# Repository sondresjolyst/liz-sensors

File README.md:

# ReadTempAndHumidity

## Garge Voltmeter

### Voltage Divider Calculation for Wemos D1 Mini

To measure a higher voltage than 3.3V using the Wemos D1 Mini's ADC port, you can create a voltage divider with 47kΩ and 4.7kΩ resistors.

#### Voltage Divider Formula

$`V_{out} = V_{in} \times \frac{R2}{(R1 + R2)}`$

##### Precision

The Wemos D1 Mini's ADC can read voltages between 0 and 3.3V and gives a 10-bit reading (0-1024).
To calculate the minimum precision in voltage, one need to divide the maximum voltage by the ADC resolution:
$`\text{Minimum precision} = \frac{3.3V}{1024} \approx 0.00322V`$

The voltage at the ADC pin is approximately 9.09% of the input voltage. When the ADC reading changes by one step (e.g., from 366 to 365), the input voltage changes by:

$`\Delta V_{in} \approx \Delta V_{ADC} \times \frac{R1 + R2}{R2}`$

$`\Delta V_{in} \approx 0.00322V \times \frac{47k\Omega + 4.7k\Omega}{4.7k\Omega} \approx 0.0355V`$

#### Given Values

- $`R1 = 47kΩ`$ (47000Ω)
- $`R2 = 4.7kΩ`$ (4700Ω)
- $`V_{out} = 3.3V`$ (ADC input maximum)

#### Calculate Maximum

$`V_{in} = \frac{V_{out} \times (R1 + R2)}{R2}`$

Plugging in the values:

$`V_{in} = \frac{3.3V \times (47000Ω + 4700Ω)}{4700Ω}`$

$`V_{in} = 3.3V \times \frac{51700Ω}{4700Ω}`$

$`V_{in} \approx 36.3V`$

### Power Consumption Calculation

To estimate the power consumption of the Wemos D1 Mini:

#### Current Draw

Assuming an average current draw of 80mA (0.08A) when performing computations and connected to Wi-Fi.

#### Power Calculation

Using a 5V supply voltage:
$`\text{Power (P)} = \text{Voltage (V)} \times \text{Current (I)}`$

$`P = 5V \times 0.08A = 0.4W`$

#### Battery Life Estimation

With a 13V battery converted to 5V, taking into account the efficiency of the DC-DC converter (assumed to be 90% efficient):

$`\text{Effective Power Required} = \frac{\text{Power Consumption}}{\text{Efficiency}}`$

$`\text{Effective Power Required} = \frac{0.4W}{0.9} \approx 0.444W`$

#### Battery Current

$`I_{13V} = \frac{0.444W}{13V} \approx 0.034A = 34mA`$

#### Battery Capacity

If using a 13V motorcycle battery with a 6Ah (6000mAh) capacity:

Estimated Runtime:

$`\text{Runtime} = \frac{\text{Battery Capacity}}{\text{Current Draw}}`$

$`\text{Runtime} = \frac{6000mAh}{34mA} \approx 176 \, \text{hours}`$

To keep the battery above 40% charge, use only 60% of the battery's capacity:

$`\text{Usable Capacity} = 0.6 \times 72Wh = 43.2Wh`$

Revised Runtime:

$`\text{Runtime} = \frac{43.2Wh}{0.4W} = 108 \, \text{hours}`$

## Garge Sensor BME280

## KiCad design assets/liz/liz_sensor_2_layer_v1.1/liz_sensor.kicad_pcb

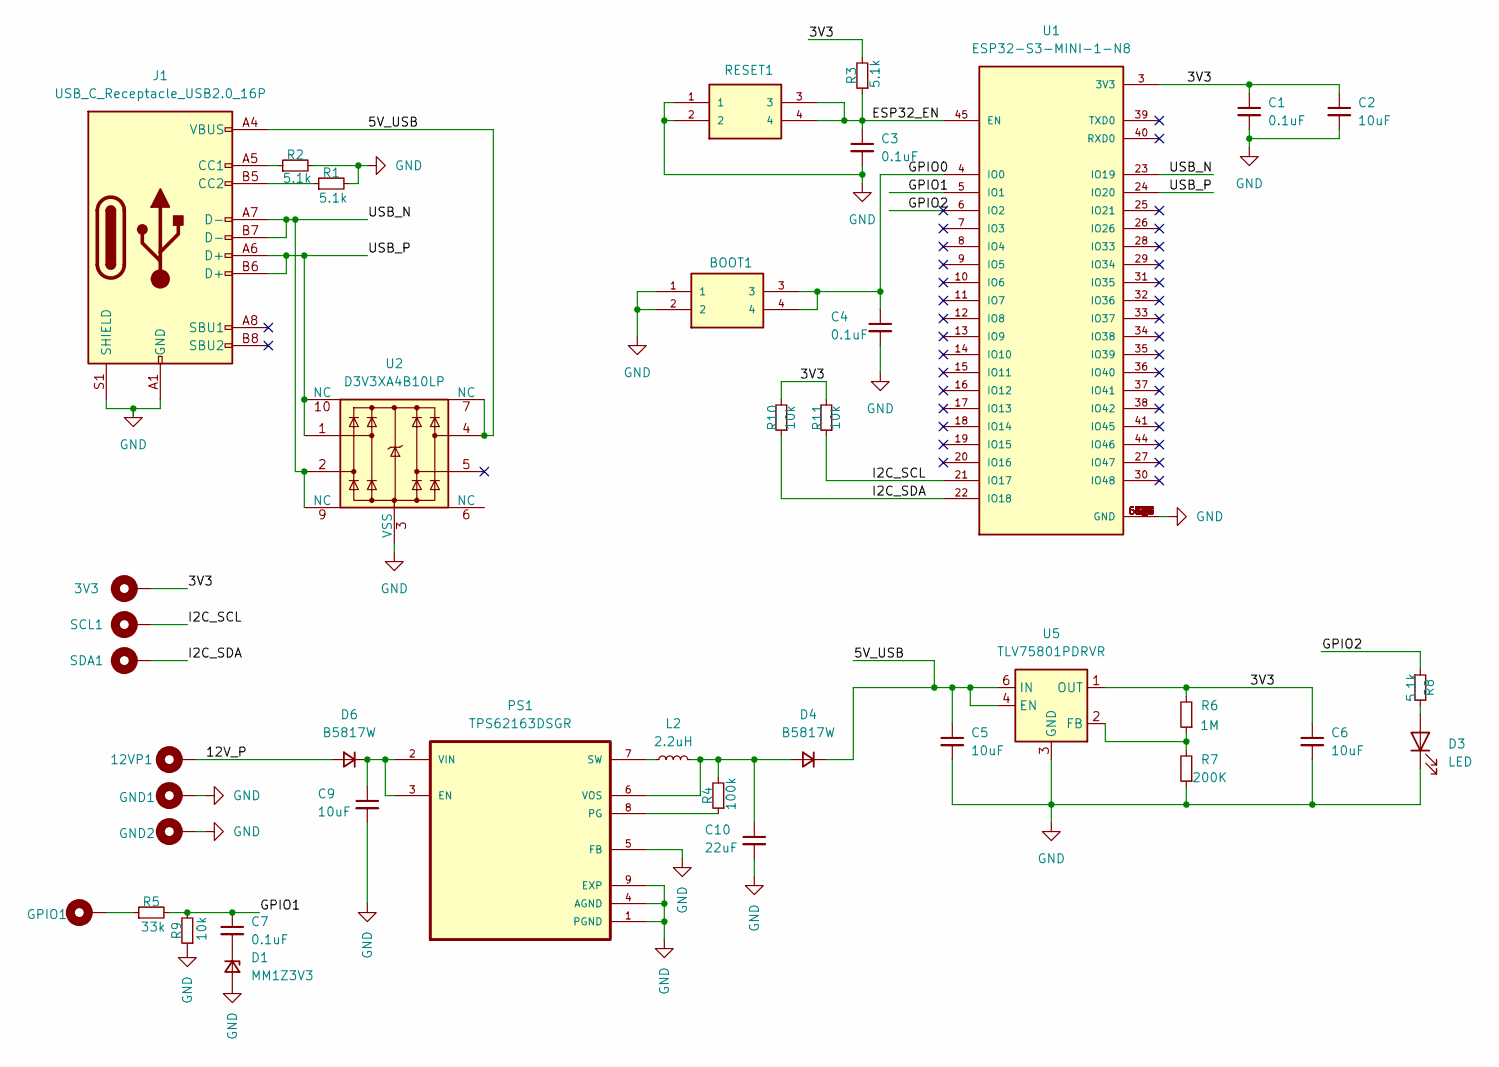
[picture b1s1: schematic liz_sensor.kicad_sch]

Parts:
3V3, 12VP1: TestPoint_THTPad_D1.0mm_Drill0.5mm
BOOT1: PTS810SJM250SMTRLFS; PTS810SJG250SMTRLFS; MANUFACTURER_PART_NUMBER PTS810SJK250SMTRLFS; JLCPCB Part # C116501
C1, C3, C4, C7: 0.1uF; C_0603_1608Metric; Part# CC0603KRX7R7BB104; JLCPCB Part # C108079
C2, C5, C6: 10uF; C_0603_1608Metric; Part# CL10A106KQ8NNNC; JLCPCB Part # C95839
C9: 10uF; C_0603_1608Metric; Part# CL10X106MO8NRNC; JLCPCB Part # C3039688
C10: 22uF; C_0603_1608Metric; Part# CL10A226MP8NUNE; JLCPCB Part # C86295
D1: MM1Z3V3; D_SOD-123; Part# MM1Z3V3; JLCPCB Part # C22379456
D3: LED; LED_0603_1608Metric; Part# HL-PST-1608H203BC; JLCPCB Part # C497940
D4, D6: B5817W; D_SOD-123; Part# B5817W; JLCPCB Part # C7420328
GND1, GND2: TestPoint_THTPad_D1.0mm_Drill0.5mm
GPIO1: TestPoint_THTPad_D1.0mm_Drill0.5mm
J1: USB_C_Receptacle_USB2.0_16P; USB_C_Receptacle_GCT_USB4105-xx-A_16P_TopMnt_Horizontal; Part# GT-USB-7010ASV; JLCPCB Part # C2988369
L2: 2.2uH; RES_CIGT201610_SAM; Part# WIP201610P-2R2ML; JLCPCB Part # C315717
PS1: TPS62163DSGR; DSG0008A; PARTREV E; JLCPCB Part # C97534
R1, R2, R3, R8: 5.1k; R_0603_1608Metric; Part# RC0603FR-075K1L; JLCPCB Part # C105580
R4: 100k; R_0603_1608Metric; Part# RC0603FR-07100KL; JLCPCB Part # C14675
R5: 33k; R_0603_1608Metric; Part# RC0603FR-0733KL; JLCPCB Part # C126359
R6: 1M; R_0603_1608Metric; Part# RC0603FR-071ML; JLCPCB Part # C105578
R7: 200K; R_0603_1608Metric; Part# RC0603FR-07200KL; JLCPCB Part # C105574
R9, R10, R11: 10k; R_0603_1608Metric; Part# RC0603FR-0710KL; JLCPCB Part # C98220
RESET1: PTS810SJM250SMTRLFS; PTS810SJG250SMTRLFS; MANUFACTURER_PART_NUMBER PTS810SJK250SMTRLFS; JLCPCB Part # C116501
SCL1: TestPoint_THTPad_D1.0mm_Drill0.5mm
SDA1: TestPoint_THTPad_D1.0mm_Drill0.5mm
U1: ESP32-S3-MINI-1-N8; XCVR_ESP32-S3-MINI-1-N8; PARTREV v0.6; JLCPCB Part # C2913206
U2: D3V3XA4B10LP; Diodes_UDFN-10_1.0x2.5mm_P0.5mm; Part# D3V3XA4B10LP-7; JLCPCB Part # C1980462
U5: TLV75801PDRVR; WSON-6-1EP_2x2mm_P0.65mm_EP1x1.6mm; Part# TLV75801PDRVR; JLCPCB Part # C2876308

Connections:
/3V3: 3V3.1, C1.1, C2.1, C6.1, R3.2, R6.2, R10.2, R11.2, U1.3 (3V3), U5.1 (OUT)
/5V_USB: C5.1, D4.1 (K), J1.A4 (VBUS), J1.A9 (VBUS), J1.B4 (VBUS), J1.B9 (VBUS), U2.4, U2.7 (NC), U5.4 (EN), U5.6 (IN)
/12V_P: 12VP1.1, D6.2 (A)
/ESP32_EN: C3.1, R3.1, RESET1.3, RESET1.4, U1.45 (EN)
/GPIO0: BOOT1.3, BOOT1.4, C4.1, U1.4 (IO0)
/GPIO1: C7.1, R5.2, R9.2, U1.5 (IO1)
/GPIO2: R8.1, U1.6 (IO2)
/I2C_SCL: R11.1, SCL1.1, U1.21 (IO17)
/I2C_SDA: R10.1, SDA1.1, U1.22 (IO18)
/USB_N: J1.A7 (D-), J1.B7 (D-), U1.23 (IO19), U2.2, U2.9 (NC)
/USB_P: J1.A6 (D+), J1.B6 (D+), U1.24 (IO20), U2.1, U2.10 (NC)
GND: BOOT1.1, BOOT1.2, C1.2, C2.2, C3.2, C4.2, C5.2, C6.2, C9.2, C10.2, D1.2 (A), D3.1 (K), GND1.1, GND2.1, J1.A1 (GND), J1.A12 (GND), J1.B1 (GND), J1.B12 (GND), J1.S1 (SHIELD), PS1.1 (PGND), PS1.4 (AGND), PS1.5 (FB), PS1.9 (EXP), R1.2, R2.2, R7.1, R9.1, RESET1.1, RESET1.2, U1.1 (GND), U1.2 (GND), U1.42 (GND), U1.43 (GND), U1.46 (GND), U1.47 (GND), U1.48 (GND), U1.49 (GND), U1.50 (GND), U1.51 (GND), U1.52 (GND), U1.53 (GND), U1.54 (GND), U1.55 (GND), U1.56 (GND), U1.57 (GND), U1.58 (GND), U1.59 (GND), U1.60 (GND), U1.61 (GND), U1.61_1 (GND), U1.61_2 (GND), U1.61_3 (GND), U1.61_4 (GND), U1.61_5 (GND), U1.61_6 (GND), U1.61_7 (GND), U1.61_8 (GND), U1.62 (GND), U1.63 (GND), U1.64 (GND), U1.65 (GND), U2.3 (VSS), U2.8 (VSS), U5.3 (GND), U5.7 (GND)
unnamed: C7.2, D1.1 (K)
unnamed: D3.2 (A), R8.2
unnamed: C10.1, D4.2 (A), L2.2, PS1.6 (VOS), R4.2
unnamed: C9.1, D6.1 (K), PS1.2 (VIN), PS1.3 (EN)
unnamed: GPIO1.1, R5.1
unnamed: J1.A5 (CC1), R2.1
unnamed: J1.B5 (CC2), R1.1
unnamed: PS1.8 (PG), R4.1
unnamed: L2.1, PS1.7 (SW)
unnamed: R6.1, R7.2, U5.2 (FB)

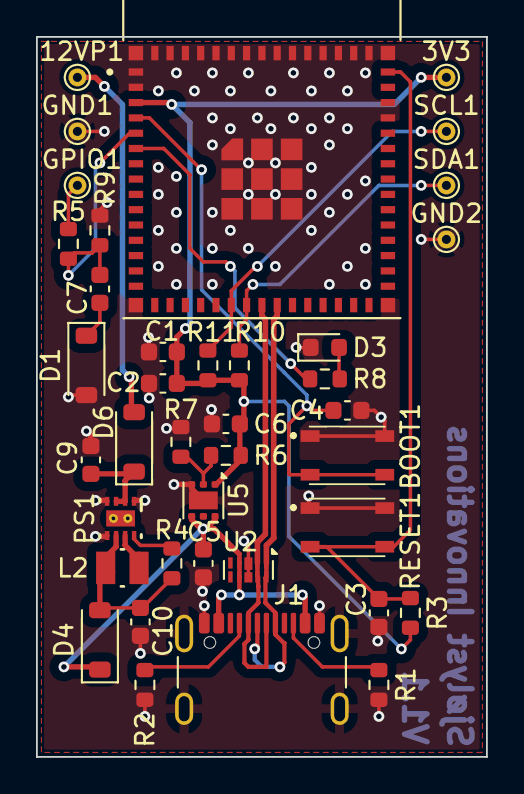
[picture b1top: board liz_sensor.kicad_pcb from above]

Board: 2 copper layers, 25.0 x 40.0 mm, 39 parts (0 on the bottom side), 22 nets.

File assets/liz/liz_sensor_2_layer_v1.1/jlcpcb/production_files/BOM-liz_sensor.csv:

Comment,Designator,Footprint,LCSC,Quantity
200K,R7,R_0603_1608Metric,C105574,1
1M,R6,R_0603_1608Metric,C105578,1
5.1k,"R1,R2,R3,R8",R_0603_1608Metric,C105580,4
0.1uF,"C1,C3,C4,C7",C_0603_1608Metric,C108079,4
PTS810SJM250SMTRLFS,"BOOT1,RESET1",PTS810SJG250SMTRLFS,C116501,2
33k,R5,R_0603_1608Metric,C126359,1
100k,R4,R_0603_1608Metric,C14675,1
D3V3XA4B10LP,U2,Diodes_UDFN-10_1.0x2.5mm_P0.5mm,C1980462,1
MM1Z3V3,D1,D_SOD-123,C22379456,1
TLV75801PDRVR,U5,WSON-6-1EP_2x2mm_P0.65mm_EP1x1.6mm,C2876308,1
ESP32-S3-MINI-1-N8,U1,XCVR_ESP32-S3-MINI-1-N8,C2913206,1
USB_C_Receptacle_USB2.0_16P,J1,USB_C_Receptacle_GCT_USB4105-xx-A_16P_TopMnt_Horizontal,C2988369,1
10uF,C9,C_0603_1608Metric,C3039688,1
2.2uH,L2,RES_CIGT201610_SAM,C315717,1
LED,D3,LED_0603_1608Metric,C497940,1
B5817W,"D4,D6",D_SOD-123,C7420328,2
22uF,C10,C_0603_1608Metric,C86295,1
10uF,"C2,C5,C6",C_0603_1608Metric,C95839,3
TPS62163DSGR,PS1,DSG0008A,C97534,1
10k,"R10,R11,R9",R_0603_1608Metric,C98220,3

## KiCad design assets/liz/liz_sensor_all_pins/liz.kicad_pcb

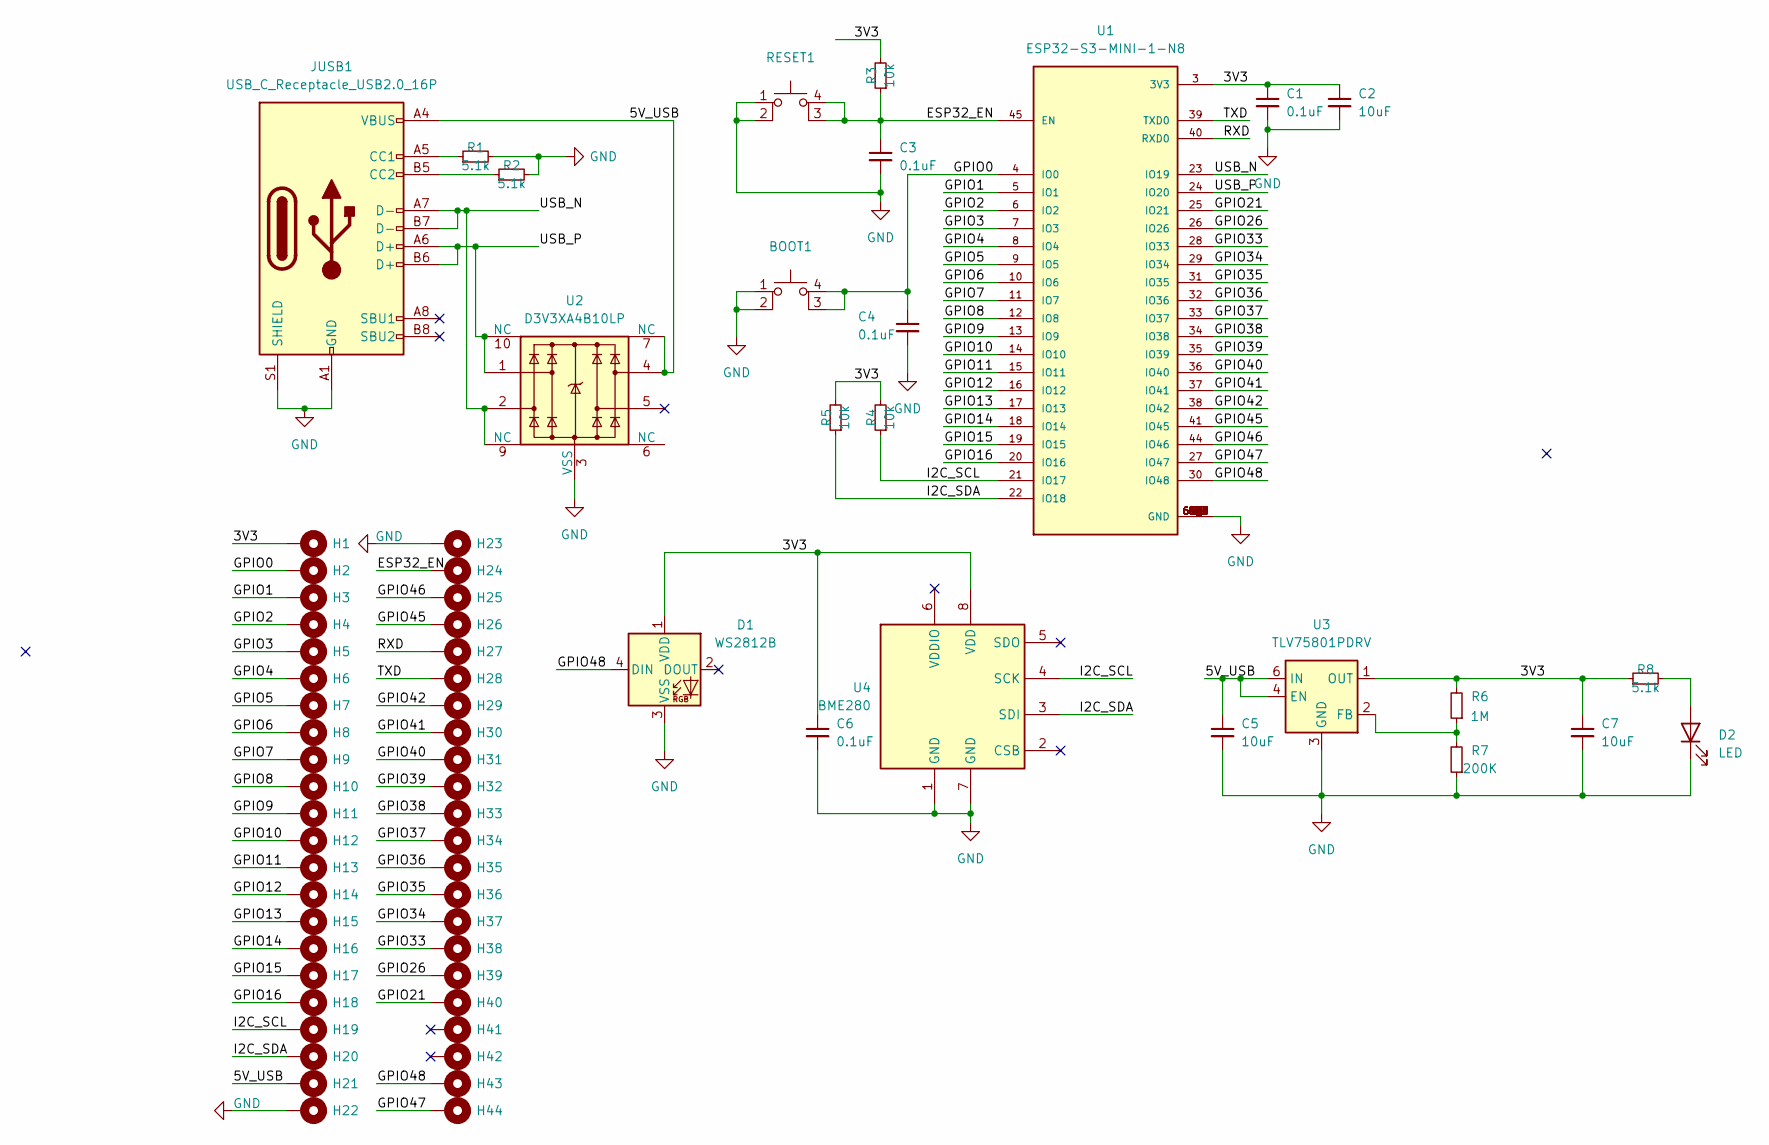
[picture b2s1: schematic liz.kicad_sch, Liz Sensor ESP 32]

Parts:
BOOT1: SW_SPST_PTS810
C1, C3, C4, C6: 0.1uF; C_0603_1608Metric
C2, C5, C7: 10uF; C_0603_1608Metric
D1: WS2812B; LED_WS2812B_PLCC4_5.0x5.0mm_P3.2mm
D2: LED; LED_0603_1608Metric
H1, H2, H3, H4, H5, H6, H7, H8, H9, H10, H11, H12, H13, H14, H15, H16, H17, H18, H19, H20, H21, H22, H23, H24, H25, H26, H27, H28, H29, H30, H31, H32, H33, H34, H35, H36, H37, H38, H39, H40, H41, H42, H43, H44: TestPoint_THTPad_D1.0mm_Drill0.5mm
JUSB1: USB_C_Receptacle_USB2.0_16P; USB_C_Receptacle_GCT_USB4105-xx-A_16P_TopMnt_Horizontal
R1, R2, R8: 5.1k; R_0603_1608Metric
R3, R4, R5: 10k; R_0603_1608Metric
R6: 1M; R_0603_1608Metric
R7: 200K; R_0603_1608Metric
RESET1: SW_SPST_PTS810
U1: ESP32-S3-MINI-1-N8; XCVR_ESP32-S3-MINI-1-N8; PARTREV v0.6
U2: D3V3XA4B10LP; Diodes_UDFN-10_1.0x2.5mm_P0.5mm
U3: TLV75801PDRV; WSON-6-1EP_2x2mm_P0.65mm_EP1x1.6mm
U4: BME280; Bosch_LGA-8_2.5x2.5mm_P0.65mm_ClockwisePinNumbering

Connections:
/3V3: C1.1, C2.1, C6.1, C7.1, D1.1 (VDD), H1.1, R3.2, R4.2, R5.2, R6.2, R8.1, U1.3 (3V3), U3.1 (OUT), U4.8 (VDD)
/5V_USB: C5.1, H21.1, JUSB1.A4 (VBUS), JUSB1.A9 (VBUS), JUSB1.B4 (VBUS), JUSB1.B9 (VBUS), U2.4, U2.7 (NC), U3.4 (EN), U3.6 (IN)
/ESP32_EN: C3.1, H24.1, R3.1, RESET1.3 (K), RESET1.4 (A), U1.45 (EN)
/GPIO0: BOOT1.3 (K), BOOT1.4 (A), C4.1, H2.1, U1.4 (IO0)
/GPIO1: H3.1, U1.5 (IO1)
/GPIO2: H4.1, U1.6 (IO2)
/GPIO3: H5.1, U1.7 (IO3)
/GPIO4: H6.1, U1.8 (IO4)
/GPIO5: H7.1, U1.9 (IO5)
/GPIO6: H8.1, U1.10 (IO6)
/GPIO7: H9.1, U1.11 (IO7)
/GPIO8: H10.1, U1.12 (IO8)
/GPIO9: H11.1, U1.13 (IO9)
/GPIO10: H12.1, U1.14 (IO10)
/GPIO11: H13.1, U1.15 (IO11)
/GPIO12: H14.1, U1.16 (IO12)
/GPIO13: H15.1, U1.17 (IO13)
/GPIO14: H16.1, U1.18 (IO14)
/GPIO15: H17.1, U1.19 (IO15)
/GPIO16: H18.1, U1.20 (IO16)
/GPIO21: H40.1, U1.25 (IO21)
/GPIO26: H39.1, U1.26 (IO26)
/GPIO33: H38.1, U1.28 (IO33)
/GPIO34: H37.1, U1.29 (IO34)
/GPIO35: H36.1, U1.31 (IO35)
/GPIO36: H35.1, U1.32 (IO36)
/GPIO37: H34.1, U1.33 (IO37)
/GPIO38: H33.1, U1.34 (IO38)
/GPIO39: H32.1, U1.35 (IO39)
/GPIO40: H31.1, U1.36 (IO40)
/GPIO41: H30.1, U1.37 (IO41)
/GPIO42: H29.1, U1.38 (IO42)
/GPIO45: H26.1, U1.41 (IO45)
/GPIO46: H25.1, U1.44 (IO46)
/GPIO47: H44.1, U1.27 (IO47)
/GPIO48: D1.4 (DIN), H43.1, U1.30 (IO48)
/I2C_SCL: H19.1, R4.1, U1.21 (IO17), U4.4 (SCK)
/I2C_SDA: H20.1, R5.1, U1.22 (IO18), U4.3 (SDI)
/RXD: H27.1, U1.40 (RXD0)
/TXD: H28.1, U1.39 (TXD0)
/USB_N: JUSB1.A7 (D-), JUSB1.B7 (D-), U1.23 (IO19), U2.2, U2.9 (NC)
/USB_P: JUSB1.A6 (D+), JUSB1.B6 (D+), U1.24 (IO20), U2.1, U2.10 (NC)
GND: BOOT1.1, BOOT1.2, C1.2, C2.2, C3.2, C4.2, C5.2, C6.2, C7.2, D1.3 (VSS), D2.1 (K), H22.1, H23.1, JUSB1.A1 (GND), JUSB1.A12 (GND), JUSB1.B1 (GND), JUSB1.B12 (GND), JUSB1.S1 (SHIELD), R1.2, R2.2, R7.1, RESET1.1, RESET1.2, U1.1 (GND), U1.2 (GND), U1.42 (GND), U1.43 (GND), U1.46 (GND), U1.47 (GND), U1.48 (GND), U1.49 (GND), U1.50 (GND), U1.51 (GND), U1.52 (GND), U1.53 (GND), U1.54 (GND), U1.55 (GND), U1.56 (GND), U1.57 (GND), U1.58 (GND), U1.59 (GND), U1.60 (GND), U1.61 (GND), U1.61_1 (GND), U1.61_2 (GND), U1.61_3 (GND), U1.61_4 (GND), U1.61_5 (GND), U1.61_6 (GND), U1.61_7 (GND), U1.61_8 (GND), U1.62 (GND), U1.63 (GND), U1.64 (GND), U1.65 (GND), U2.3 (VSS), U2.8 (VSS), U3.3 (GND), U3.7 (GND), U4.1 (GND), U4.7 (GND)
unnamed: D2.2 (A), R8.2
unnamed: JUSB1.A5 (CC1), R1.1
unnamed: JUSB1.B5 (CC2), R2.1
unnamed: R6.1, R7.2, U3.2 (FB)

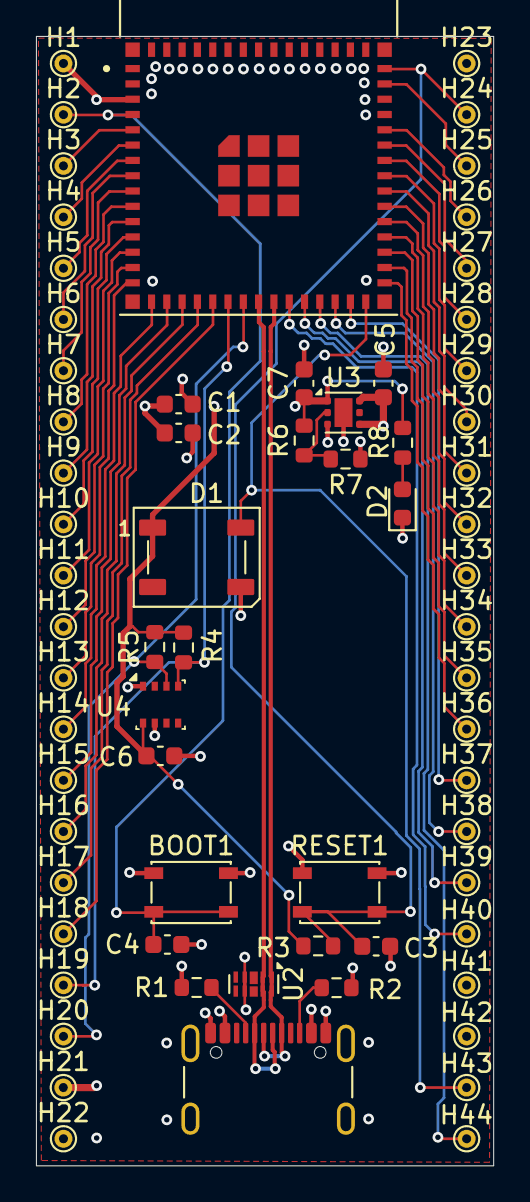
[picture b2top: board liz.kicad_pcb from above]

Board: 4 copper layers, 25.4 x 62.7 mm, 68 parts (0 on the bottom side), 47 nets.

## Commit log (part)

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2023-11-20 git setup
2023-11-26 controll device
2023-11-27 openwiz documentation
2023-12-03 format
2023-12-24 tempOffet, humidOffset, mqtt reconnect
2024-03-27 feat: add support for BME280 sensor
2024-04-20 feat: restart ESP if temp or humid fail 10 times
2024-11-24 feat: add voltmeter function
2024-11-24 chore(master): release 1.0.0
2024-12-01 chore: mqttcallback test
2024-12-03 ci: give lint contents read (#3)
    * ci: add linter and update release workflow
    * ci: give lint contents read
2024-12-03 ci: use commit hash instead of tag (#5)
2024-12-03 docs: circuit diagrams (#6)
    * docs: circuit diagrams
    * chore: add new line
2024-12-15 chore(deps): bump equinor/ops-actions from 9.11.0 to 9.12.1 (#8)
    Bumps [equinor/ops-actions](https://github.com/equinor/ops-actions) from 9.11.0 to 9.12.1.
    - [Release notes](https://github.com/equinor/ops-actions/releases)
    - [Changelog](https://github.com/equinor/ops-actions/blob/main/CHANGELOG.md)
    - [Commits](https://github.com/equinor/ops-actions/compare/ed242b9acb1b98a438b595eba389631acc614221...21ca4ff773cab0ffe4f4e8e9b2d04c392c075a5e)
    ---
    updated-dependencies:
2024-12-16 chore: increase discover interval
2024-12-16 feat: update liz library (#13)
2024-12-18 feat: clear discovered devices on mqtt connect (#15)
    * feat: clearDiscoveredDevices on mqtt connect
    * chore: update liz
    * chore: print when clearing devices
    * chore: update liz
2024-12-22 chore(deps): bump equinor/ops-actions from 9.12.1 to 9.12.2 (#18)
    Bumps [equinor/ops-actions](https://github.com/equinor/ops-actions) from 9.12.1 to 9.12.2.
    - [Release notes](https://github.com/equinor/ops-actions/releases)
    - [Changelog](https://github.com/equinor/ops-actions/blob/main/CHANGELOG.md)
    - [Commits](https://github.com/equinor/ops-actions/compare/21ca4ff773cab0ffe4f4e8e9b2d04c392c075a5e...f3943374c9677ff00822cb04f0757933b1bc4926)
    ---
    updated-dependencies:
2024-12-31 feat: add disconnect wifi button
2024-12-31 chore: add .clang-format
2025-01-01 chore(master): release 1.1.0 (#11)
2025-01-02 docs: voltmeter precision
2025-01-05 chore: update copyright date
2025-01-12 chore(deps): bump equinor/ops-actions from 9.12.2 to 9.12.4
    Bumps [equinor/ops-actions](https://github.com/equinor/ops-actions) from 9.12.2 to 9.12.4.
    - [Release notes](https://github.com/equinor/ops-actions/releases)
    - [Changelog](https://github.com/equinor/ops-actions/blob/main/CHANGELOG.md)
    - [Commits](https://github.com/equinor/ops-actions/compare/f3943374c9677ff00822cb04f0757933b1bc4926...21643513a0eb001c43e16a6f15e8dc9bade379ed)
    ---
    updated-dependencies:
2025-01-20 chore(deps): bump equinor/ops-actions from 9.12.4 to 9.13.1 (#21)
    Bumps [equinor/ops-actions](https://github.com/equinor/ops-actions) from 9.12.4 to 9.13.1.
    - [Release notes](https://github.com/equinor/ops-actions/releases)
    - [Changelog](https://github.com/equinor/ops-actions/blob/main/CHANGELOG.md)
    - [Commits](https://github.com/equinor/ops-actions/compare/21643513a0eb001c43e16a6f15e8dc9bade379ed...4a7305af70c196d18a05ae49b2f7b8646bae8f5e)
    ---
    updated-dependencies:
2025-02-07 chore: change resistor values
2025-02-23 chore(deps): bump equinor/ops-actions from 9.13.2 to 9.13.3
    Bumps [equinor/ops-actions](https://github.com/equinor/ops-actions) from 9.13.2 to 9.13.3.
    - [Release notes](https://github.com/equinor/ops-actions/releases)
    - [Changelog](https://github.com/equinor/ops-actions/blob/main/CHANGELOG.md)
    - [Commits](https://github.com/equinor/ops-actions/compare/31a534e69a819881f7da65b74c1a7ec92edcccab...02a191feae09acb6d1992eebd5d847152351c889)
    ---
    updated-dependencies:
2025-03-02 chore(deps): bump googleapis/release-please-action from 4.1.3 to 4.1.4 (#24)
    Bumps [googleapis/release-please-action](https://github.com/googleapis/release-please-action) from 4.1.3 to 4.1.4.
    - [Release notes](https://github.com/googleapis/release-please-action/releases)
    - [Changelog](https://github.com/googleapis/release-please-action/blob/main/CHANGELOG.md)
    - [Commits](https://github.com/googleapis/release-please-action/compare/7987652d64b4581673a76e33ad5e98e3dd56832f...d1a8f221d7723166f48a584aebba00ef3f6febec)
    ---
    updated-dependencies:
2025-03-31 chore(deps): bump equinor/ops-actions from 9.14.0 to 9.15.0 (#30)
    Bumps [equinor/ops-actions](https://github.com/equinor/ops-actions) from 9.14.0 to 9.15.0.
    - [Release notes](https://github.com/equinor/ops-actions/releases)
    - [Changelog](https://github.com/equinor/ops-actions/blob/main/CHANGELOG.md)
    - [Commits](https://github.com/equinor/ops-actions/compare/20648f341aa77c794bae98da077409faf00652a1...e3df48c8e1911a97468d9691101a7e9f6eba62d8)
    ---
    updated-dependencies:
2025-04-14 chore(deps): bump equinor/ops-actions from 9.17.0 to 9.19.2 (#34)
    Bumps [equinor/ops-actions](https://github.com/equinor/ops-actions) from 9.17.0 to 9.19.2.
    - [Release notes](https://github.com/equinor/ops-actions/releases)
    - [Changelog](https://github.com/equinor/ops-actions/blob/main/CHANGELOG.md)
    - [Commits](https://github.com/equinor/ops-actions/compare/30c728be1ed37027601258207cf555358b2da838...de0d9240b0f3559211298584e13002a34d96165b)
    ---
    updated-dependencies:
2025-06-02 chore: backups
2025-06-07 chore: set localudpport static and add i2c to build config
2025-06-07 chore: add comments to discoverAndSubscribe (#37)
2025-06-26 chore: rename pcb folders
2025-06-26 feat: ota
2025-06-29 chore(deps): bump equinor/ops-actions from 9.19.4 to 9.20.0
    Bumps [equinor/ops-actions](https://github.com/equinor/ops-actions) from 9.19.4 to 9.20.0.
    - [Release notes](https://github.com/equinor/ops-actions/releases)
    - [Changelog](https://github.com/equinor/ops-actions/blob/main/CHANGELOG.md)
    - [Commits](https://github.com/equinor/ops-actions/compare/bc630418a9a5340958e5dc3aadf0ad93004f063d...7250ebf9722b3e8ed96a427b36f8eb2df7512e81)
    ---
    updated-dependencies:
2025-06-29 chore/eeprom-esp32
2025-06-29 chore: rename binary on build (#49)
2025-06-29 chore(main): release 1.2.0
2025-07-21 chore: update liz for better discovering
2025-07-27 chore: move to emqx and logging
2025-07-28 chore: add logging and change mqtt setup
2025-08-10 chore(main): release 1.2.0 (#50)
2025-08-13 feat: add version to device config (#56)
    * feat: add version to device config
    * chore: change version number
2025-08-24 chore(deps): bump googleapis/release-please-action from 4.2.0 to 4.3.0
    Bumps [googleapis/release-please-action](https://github.com/googleapis/release-please-action) from 4.2.0 to 4.3.0.
    - [Release notes](https://github.com/googleapis/release-please-action/releases)
    - [Changelog](https://github.com/googleapis/release-please-action/blob/main/CHANGELOG.md)
    - [Commits](https://github.com/googleapis/release-please-action/compare/a02a34c4d625f9be7cb89156071d8567266a2445...c2a5a2bd6a758a0937f1ddb1e8950609867ed15c)
    ---
    updated-dependencies:
2025-09-14 chore(deps): bump equinor/ops-actions from 9.23.0 to 9.24.2
    Bumps [equinor/ops-actions](https://github.com/equinor/ops-actions) from 9.23.0 to 9.24.2.
    - [Release notes](https://github.com/equinor/ops-actions/releases)
    - [Changelog](https://github.com/equinor/ops-actions/blob/main/CHANGELOG.md)
    - [Commits](https://github.com/equinor/ops-actions/compare/58f585c3678d9eeef72bcd29c6b25c352eb544e5...ac9f7829eb5d96f7a4995c846153848d4837b53f)
    ---
    updated-dependencies:
2025-09-28 chore(deps): bump equinor/ops-actions from 9.24.5 to 9.24.6
    Bumps [equinor/ops-actions](https://github.com/equinor/ops-actions) from 9.24.5 to 9.24.6.
    - [Release notes](https://github.com/equinor/ops-actions/releases)
    - [Changelog](https://github.com/equinor/ops-actions/blob/main/CHANGELOG.md)
    - [Commits](https://github.com/equinor/ops-actions/compare/b69b1fceb1c03e01ca3ee5771f477442521331f0...1230114ee01f7dd98715570ea7b957d7fda1ec4c)
    ---
    updated-dependencies:
2025-10-03 feat: new certificate (#63)
2025-10-06 chore(deps): bump equinor/ops-actions from 9.24.6 to 9.25.0 (#65)
    Bumps [equinor/ops-actions](https://github.com/equinor/ops-actions) from 9.24.6 to 9.25.0.
    - [Release notes](https://github.com/equinor/ops-actions/releases)
    - [Changelog](https://github.com/equinor/ops-actions/blob/main/CHANGELOG.md)
    - [Commits](https://github.com/equinor/ops-actions/compare/1230114ee01f7dd98715570ea7b957d7fda1ec4c...beabcb741a47550f8d58d3be1fca08408e564288)
    ---
    updated-dependencies:
2025-10-20 chore(deps): bump equinor/ops-actions from 9.26.0 to 9.27.0 (#67)
    Bumps [equinor/ops-actions](https://github.com/equinor/ops-actions) from 9.26.0 to 9.27.0.
    - [Release notes](https://github.com/equinor/ops-actions/releases)
    - [Changelog](https://github.com/equinor/ops-actions/blob/main/CHANGELOG.md)
    - [Commits](https://github.com/equinor/ops-actions/compare/718dda01e37c85a1c58bec19e73cbe0beef9485b...434d0fd510cbac8df2379ddee1c91f257cb0f209)
    ---
    updated-dependencies:
2025-10-27 chore(deps): bump googleapis/release-please-action from 4.3.0 to 4.4.0 (#69)
    Bumps [googleapis/release-please-action](https://github.com/googleapis/release-please-action) from 4.3.0 to 4.4.0.
    - [Release notes](https://github.com/googleapis/release-please-action/releases)
    - [Changelog](https://github.com/googleapis/release-please-action/blob/main/CHANGELOG.md)
    - [Commits](https://github.com/googleapis/release-please-action/compare/c2a5a2bd6a758a0937f1ddb1e8950609867ed15c...16a9c90856f42705d54a6fda1823352bdc62cf38)
    ---
    updated-dependencies:
2025-11-09 chore(deps): bump equinor/ops-actions/.github/workflows/super-linter.yml
    Bumps [equinor/ops-actions/.github/workflows/super-linter.yml](https://github.com/equinor/ops-actions) from 9.29.0 to 9.30.0.
    - [Release notes](https://github.com/equinor/ops-actions/releases)
    - [Changelog](https://github.com/equinor/ops-actions/blob/main/CHANGELOG.md)
    - [Commits](https://github.com/equinor/ops-actions/compare/0180226a24d7a338fe0eb3539780f37ac9e36066...e204ec946bafb37000a2f698a66aee30a13b2c73)
    ---
    updated-dependencies:
2025-11-13 chore(main): release 1.4.1
2025-11-17 chore(deps): bump equinor/ops-actions/.github/workflows/super-linter.yml (#75)
    Bumps [equinor/ops-actions/.github/workflows/super-linter.yml](https://github.com/equinor/ops-actions) from 9.30.0 to 9.31.0.
    - [Release notes](https://github.com/equinor/ops-actions/releases)
    - [Changelog](https://github.com/equinor/ops-actions/blob/main/CHANGELOG.md)
    - [Commits](https://github.com/equinor/ops-actions/compare/e204ec946bafb37000a2f698a66aee30a13b2c73...2a90f5ec5f1d13f68c00774ff573702e94b857e0)
    ---
    updated-dependencies:
2025-11-29 chore: move interval to top of loop (#77)
2025-12-08 fix(deps): bump urllib3 in the pip group across 1 directory (#78)
    Bumps the pip group with 1 update in the / directory: [urllib3](https://github.com/urllib3/urllib3).
    Updates `urllib3` from 2.5.0 to 2.6.0
    - [Release notes](https://github.com/urllib3/urllib3/releases)
    - [Changelog](https://github.com/urllib3/urllib3/blob/main/CHANGES.rst)
    - [Commits](https://github.com/urllib3/urllib3/compare/2.5.0...2.6.0)
    ---
2025-12-20 chore(main): release 1.5.0
2025-12-22 feat: sleep after x failed mqtt attempts
2025-12-22 chore: update version
2025-12-22 fix: higher unreleased versions would downgrade to latest version in manifest (#85)
2025-12-23 chore: update version number
